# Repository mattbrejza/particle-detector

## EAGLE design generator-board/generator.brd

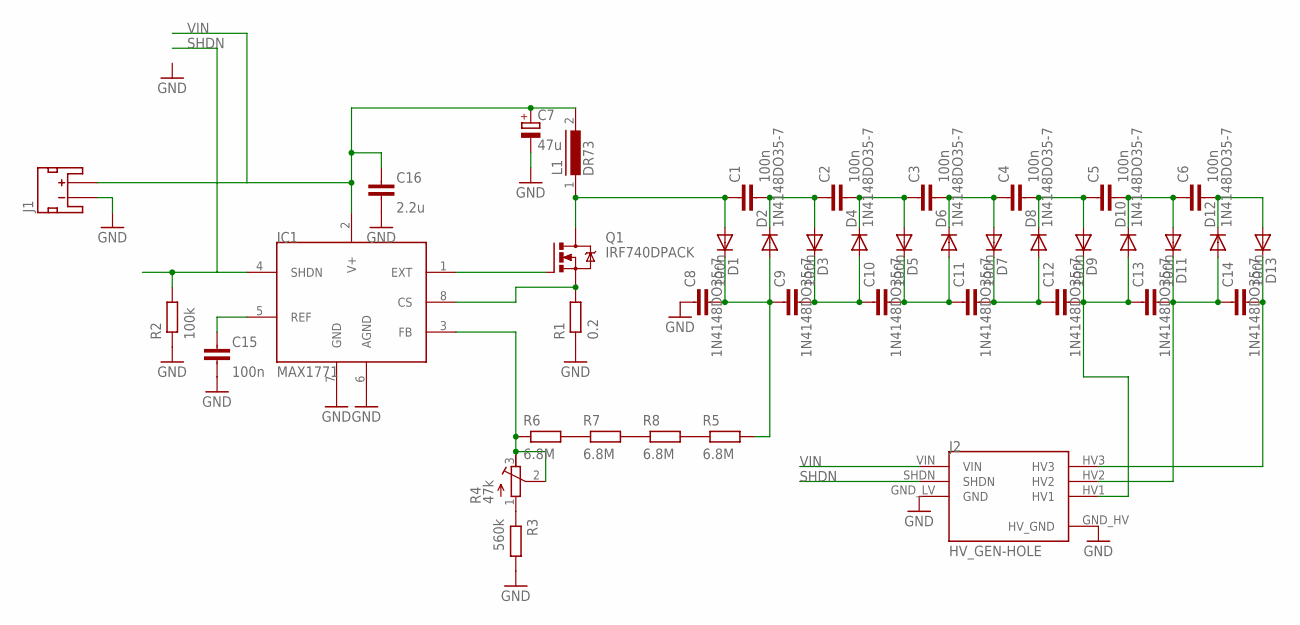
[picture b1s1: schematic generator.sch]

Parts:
C1, C2, C3, C4, C5, C6, C8, C9, C10, C11, C12, C13, C14: 100n; C1206-N; FARNELL 1855877
C7: 47u; E2-5; VOLTAGE 16V; FARNELL 9452460
C15: 100n; C0603-N; FARNELL 2495332
C16: 2.2u; C0603-N; FARNELL 2496923
D1, D2, D3, D4, D5, D6, D7, D8, D9, D10, D11, D12, D13: 1N4148DO35-7; DO35-7; FARNELL 1625213
IC1: MAX1771; SO08
J1: JST_2MM_MALE_TH; JST-2-TH
J2: HV_GEN-HOLE; BRD-LAYOUT2
L1: DR73; FARNELL 2061654
Q1: IRF740DPACK; DPACK_1; FARNELL 2453433
R1: 0.2; R0805-N; FARNELL 2328089
R2: 100k; R0603-N
R3: 560k; R0603-N
R4: 47k; RTRIM3103; FARNELL 1771727
R5, R6, R7, R8: 6.8M; R0603-N; FARNELL 2138708

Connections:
GND: C7.-, C8.1, C15.2, C16.2, IC1.6 (AGND), IC1.7 (GND), J1.2 (-), J2.GND_HV (HV_GND), J2.GND_LV (GND), R1.1, R2.1, R3.2
unnamed: IC1.8 (CS), Q1.E (S), R1.2
unnamed: IC1.1 (EXT), Q1.B (G)
unnamed: C8.2, C9.1, D1.C, D2.A, R5.2
unnamed: C15.1, IC1.5 (REF)
unnamed: C1.1, D1.A, L1.1, Q1.C (D)
unnamed: C1.2, C2.1, D2.C, D3.A
unnamed: C9.2, C10.1, D3.C, D4.A
unnamed: C2.2, C3.1, D4.C, D5.A
unnamed: C10.2, C11.1, D5.C, D6.A
unnamed: C3.2, C4.1, D6.C, D7.A
unnamed: C11.2, C12.1, D7.C, D8.A
unnamed: C4.2, C5.1, D8.C, D9.A
unnamed: C12.2, C13.1, D9.C, D10.A, J2.HV1
unnamed: C5.2, C6.1, D10.C, D11.A
unnamed: C13.2, C14.1, D11.C, D12.A, J2.HV2
unnamed: IC1.3 (FB), R4.2 (S), R4.3 (E), R6.1
unnamed: R5.1, R8.2
unnamed: R7.2, R8.1
unnamed: R6.2, R7.1
unnamed: R3.1, R4.1 (A)
unnamed: C6.2, D12.C, D13.A
unnamed: C14.2, D13.C, J2.HV3
SHDN: IC1.4 (SHDN), J2.SHDN, R2.2
VIN: C7.+, C16.1, IC1.2 (V+), J1.1 (+), J2.VIN, L1.2

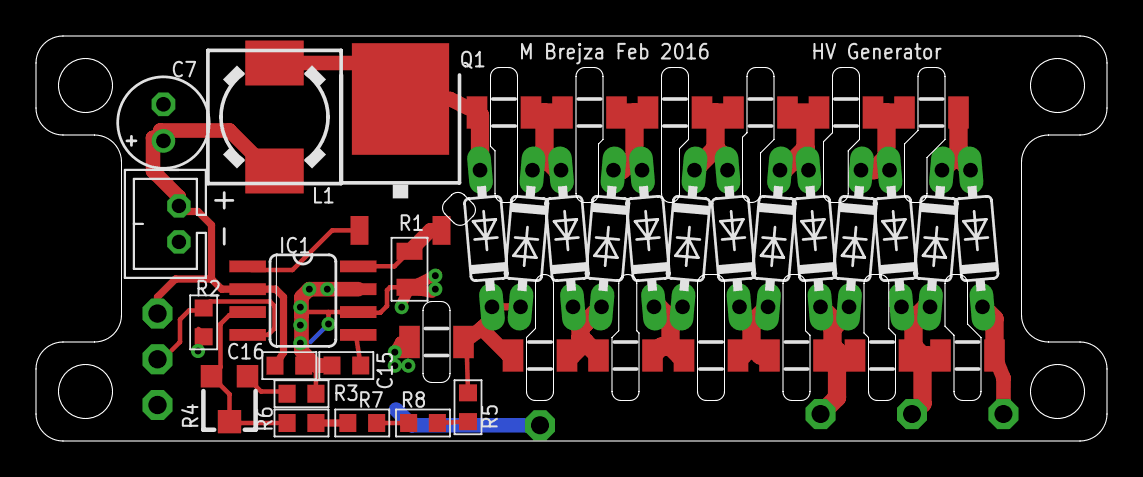
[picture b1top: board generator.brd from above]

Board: 2 copper layers, 59.5 x 22.5 mm, 42 parts (0 on the bottom side), 25 nets.

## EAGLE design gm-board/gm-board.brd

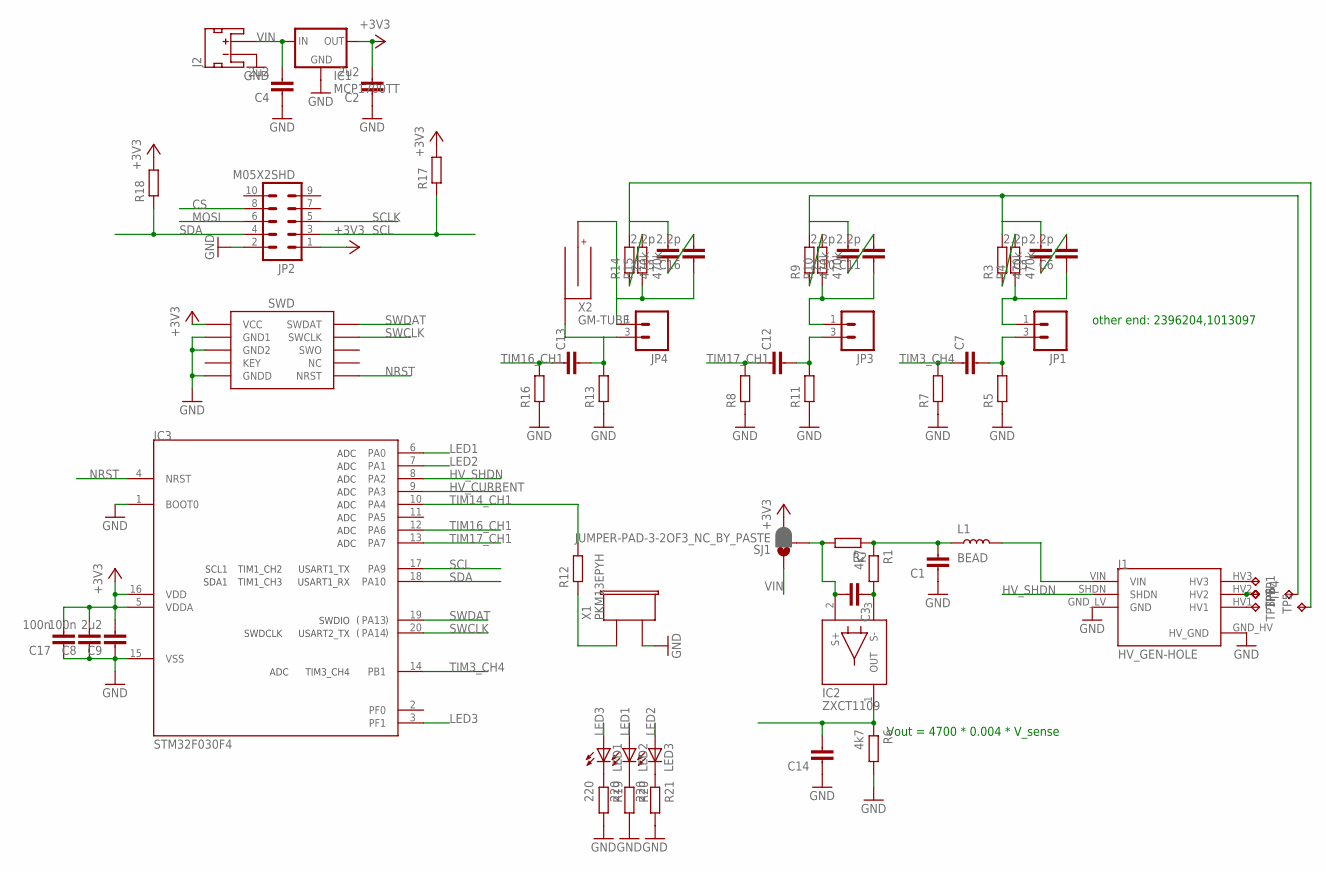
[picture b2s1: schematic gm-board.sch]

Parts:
C1, C3, C7, C12, C13, C14: CAPACITOR0603-N; C0603-N
C2, C4, C9: 2u2; C0603-N; FARNELL 2496923
C5, C6, C10, C11, C15, C16: 2.2p; C0805-N; FARNELL 1855767
C8, C17: 100n; C0603-N
IC1: MCP1700TT; SOT23
IC2: ZXCT1109; SOT23; FARNELL 1904028
IC3: STM32F030F4; TSSOP20; FARNELL 2393635
J1: HV_GEN-HOLE; BRD-LAYOUT2
J2: JST_2MM_MALE_TH-NT; JST-2-TH-NOTEXT
J3: SWD_SHROUD; SWD_PTH_SHROUD
JP1, JP3, JP4: M02-HV; M03-HV; FARNELL 1462950
JP2: M05X2SHD; 2X5-SHROUDED
L1: BEAD; L0603-N; FARNELL 1781093
LED1, LED2, LED3: LEDCHIPLED_0603; CHIPLED_0603
R1, R6: 4k7; R0603-N
R2: RESISTOR0603-N; R0603-N; FARNELL 2328089
R3, R4, R9, R10, R14: 470k; R1206-N; FARNELL 1576201
R5, R7, R8, R11, R12, R13, R16, R17, R18: RESISTOR0603-N; R0603-N
R15: 470k; R1206-N
R19, R20, R21: 220; R0603-N
SJ1: JUMPER-PAD-3-2OF3_NC_BY_PASTE; PAD-JUMPER-3-2OF3_NC_BY_PASTE_YES_SILK_FULL_BOX
TP1, TP2, TP3, TP4, TP5, TP6: TPTP09R; TP09R
X1: PKM13EPYH
X2: GM-TUBE

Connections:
+3V3: C2.2, C8.2, C9.2, C17.2, IC1.2 (OUT), IC3.5 (VDDA), IC3.16 (VDD), J3.1 (VCC), JP2.1, R17.2, R18.2, SJ1.3
CS: JP2.8
GND: C1.1, C2.1, C4.1, C8.1, C9.1, C14.1, C17.1, IC1.1 (GND), IC3.1 (BOOT0), IC3.15 (VSS), J1.GND_HV (HV_GND), J1.GND_LV (GND), J2.2 (-), J3.3 (GND1), J3.5 (GND2), J3.9 (GNDD), JP2.2, R5.1, R6.2, R7.1, R8.1, R11.1, R13.1, R16.1, R19.2, R20.2, R21.2, X1.2
HV_CURRENT: C14.2, IC2.1 (OUT), IC3.9 (PA3), R6.1
HV_SHDN: IC3.8 (PA2), J1.SHDN
LED1: IC3.6 (PA0), LED2.A
LED2: IC3.7 (PA1), LED3.A
LED3: IC3.3 (PF1), LED1.A
MOSI: JP2.6
unnamed: C13.2, JP4.3 (2), R13.2, X2.B1 (-), X2.B2 (-)
unnamed: J1.VIN, L1.2
unnamed: C16.1, JP4.1, R15.1, X2.A1 (+), X2.A2 (+)
unnamed: R14.1, R15.2
unnamed: C12.2, JP3.3 (2), R11.2
unnamed: R12.1, X1.1
unnamed: C1.2, L1.1, R1.1, R2.1
unnamed: C15.2, R14.2, TP5.TP
unnamed: C7.2, JP1.3 (2), R5.2
unnamed: J1.HV3, TP1.TP
unnamed: C3.2, IC2.2 (S+), R2.2, SJ1.2
unnamed: J1.HV2, TP2.TP, TP6.TP
unnamed: J1.HV1, TP3.TP
unnamed: LED1.C, R19.1
unnamed: LED2.C, R20.1
unnamed: C15.1, C16.2
unnamed: LED3.C, R21.1
unnamed: C3.1, IC2.3 (S-), R1.2
unnamed: C11.1, JP3.1, R10.1
unnamed: C5.2, C10.2, R3.2, R9.2, TP4.TP
unnamed: R9.1, R10.2
unnamed: C10.1, C11.2
unnamed: C6.1, JP1.1, R4.1
unnamed: R3.1, R4.2
unnamed: C5.1, C6.2
NRST: IC3.4 (NRST), J3.10 (NRST)
SCL: IC3.17 (PA9), JP2.3, R17.1
SCLK: JP2.5
SDA: IC3.18 (PA10), JP2.4, R18.1
SWCLK: IC3.20 (PA14), J3.4 (SWCLK)
SWDAT: IC3.19 (PA13), J3.2 (SWDAT)
TIM3_CH4: C7.1, IC3.14 (PB1), R7.2
TIM14_CH1: IC3.10 (PA4), R12.2
TIM16_CH1: C13.1, IC3.12 (PA6), R16.2
TIM17_CH1: C12.1, IC3.13 (PA7), R8.2
VIN: C4.2, IC1.3 (IN), J2.1 (+), SJ1.1

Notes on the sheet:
Vout = 4700 * 0.004 * V_sense
other end: 2396204,1013097

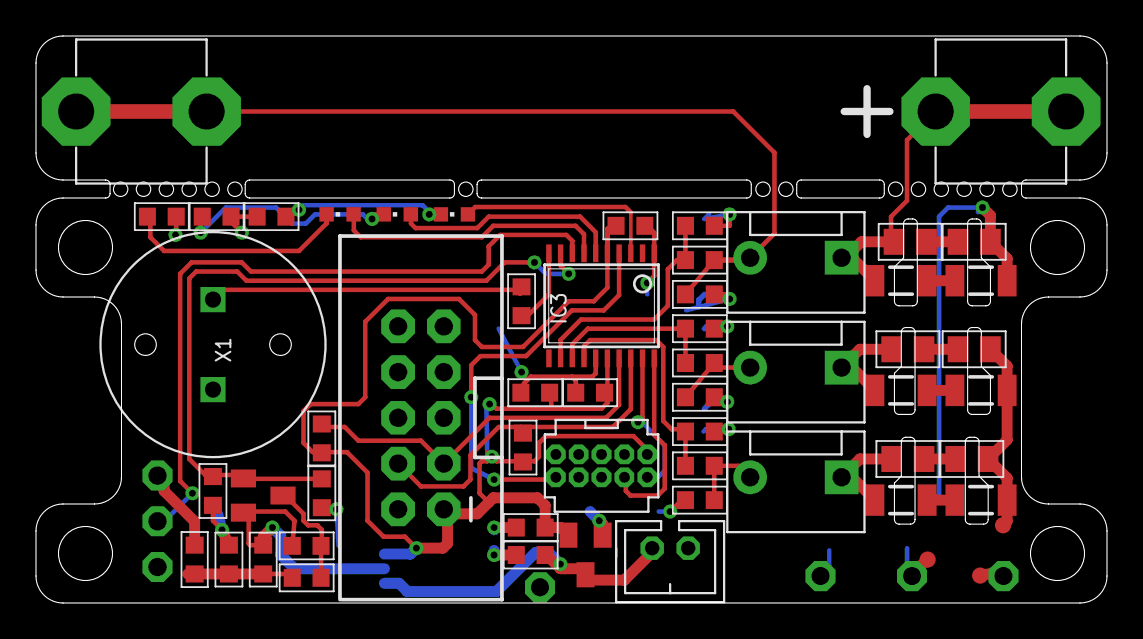
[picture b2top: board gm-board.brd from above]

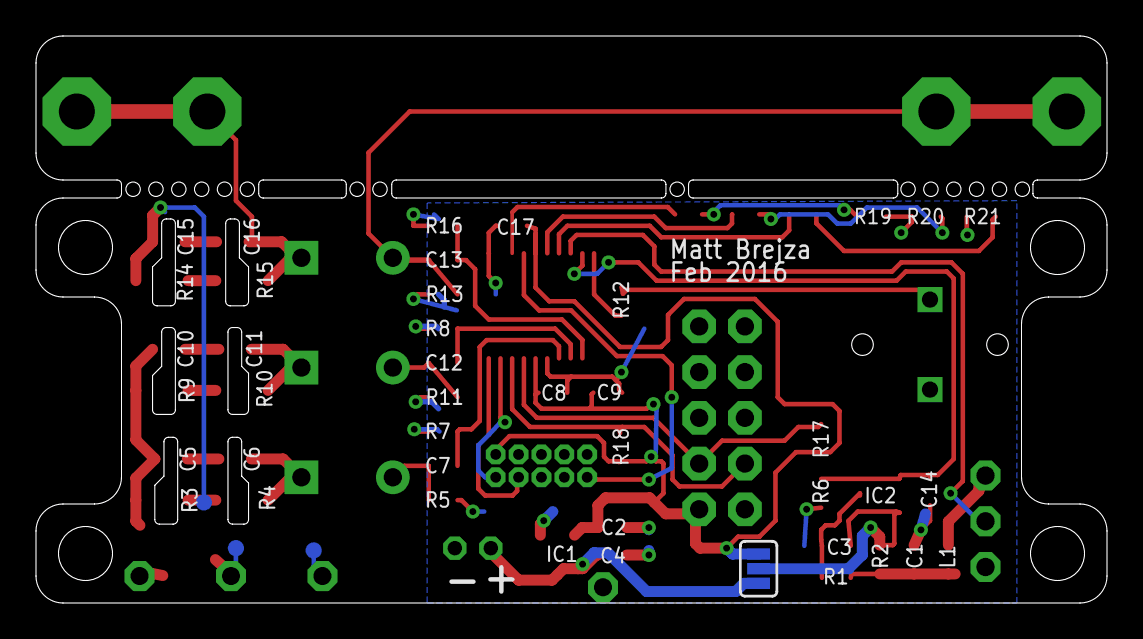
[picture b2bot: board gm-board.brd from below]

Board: 2 copper layers, 59.5 x 31.5 mm, 61 parts (4 on the bottom side), 42 nets.

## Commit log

2015-11-30 adding high voltage generator
2016-01-27 adding testpad, starting counting board
2016-02-04 done gen bom, almost done coutner
2016-02-05 adding part ordering numbers
2016-02-06 almost done
2016-02-06 added new outlone
2016-02-08 gettuing there...
2016-02-12 now to panelize
2016-02-13 about to panelize
2016-04-07 final board, started firmware
2016-04-11 adding spi comms
2016-04-30 mostly working (still adc to fix)

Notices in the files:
parts and their libraries:
SparkFun-Connectors: Licensing: Creative Commons ShareAlike 4.0 International - https://creativecommons.org/licenses/by-sa/4.0
